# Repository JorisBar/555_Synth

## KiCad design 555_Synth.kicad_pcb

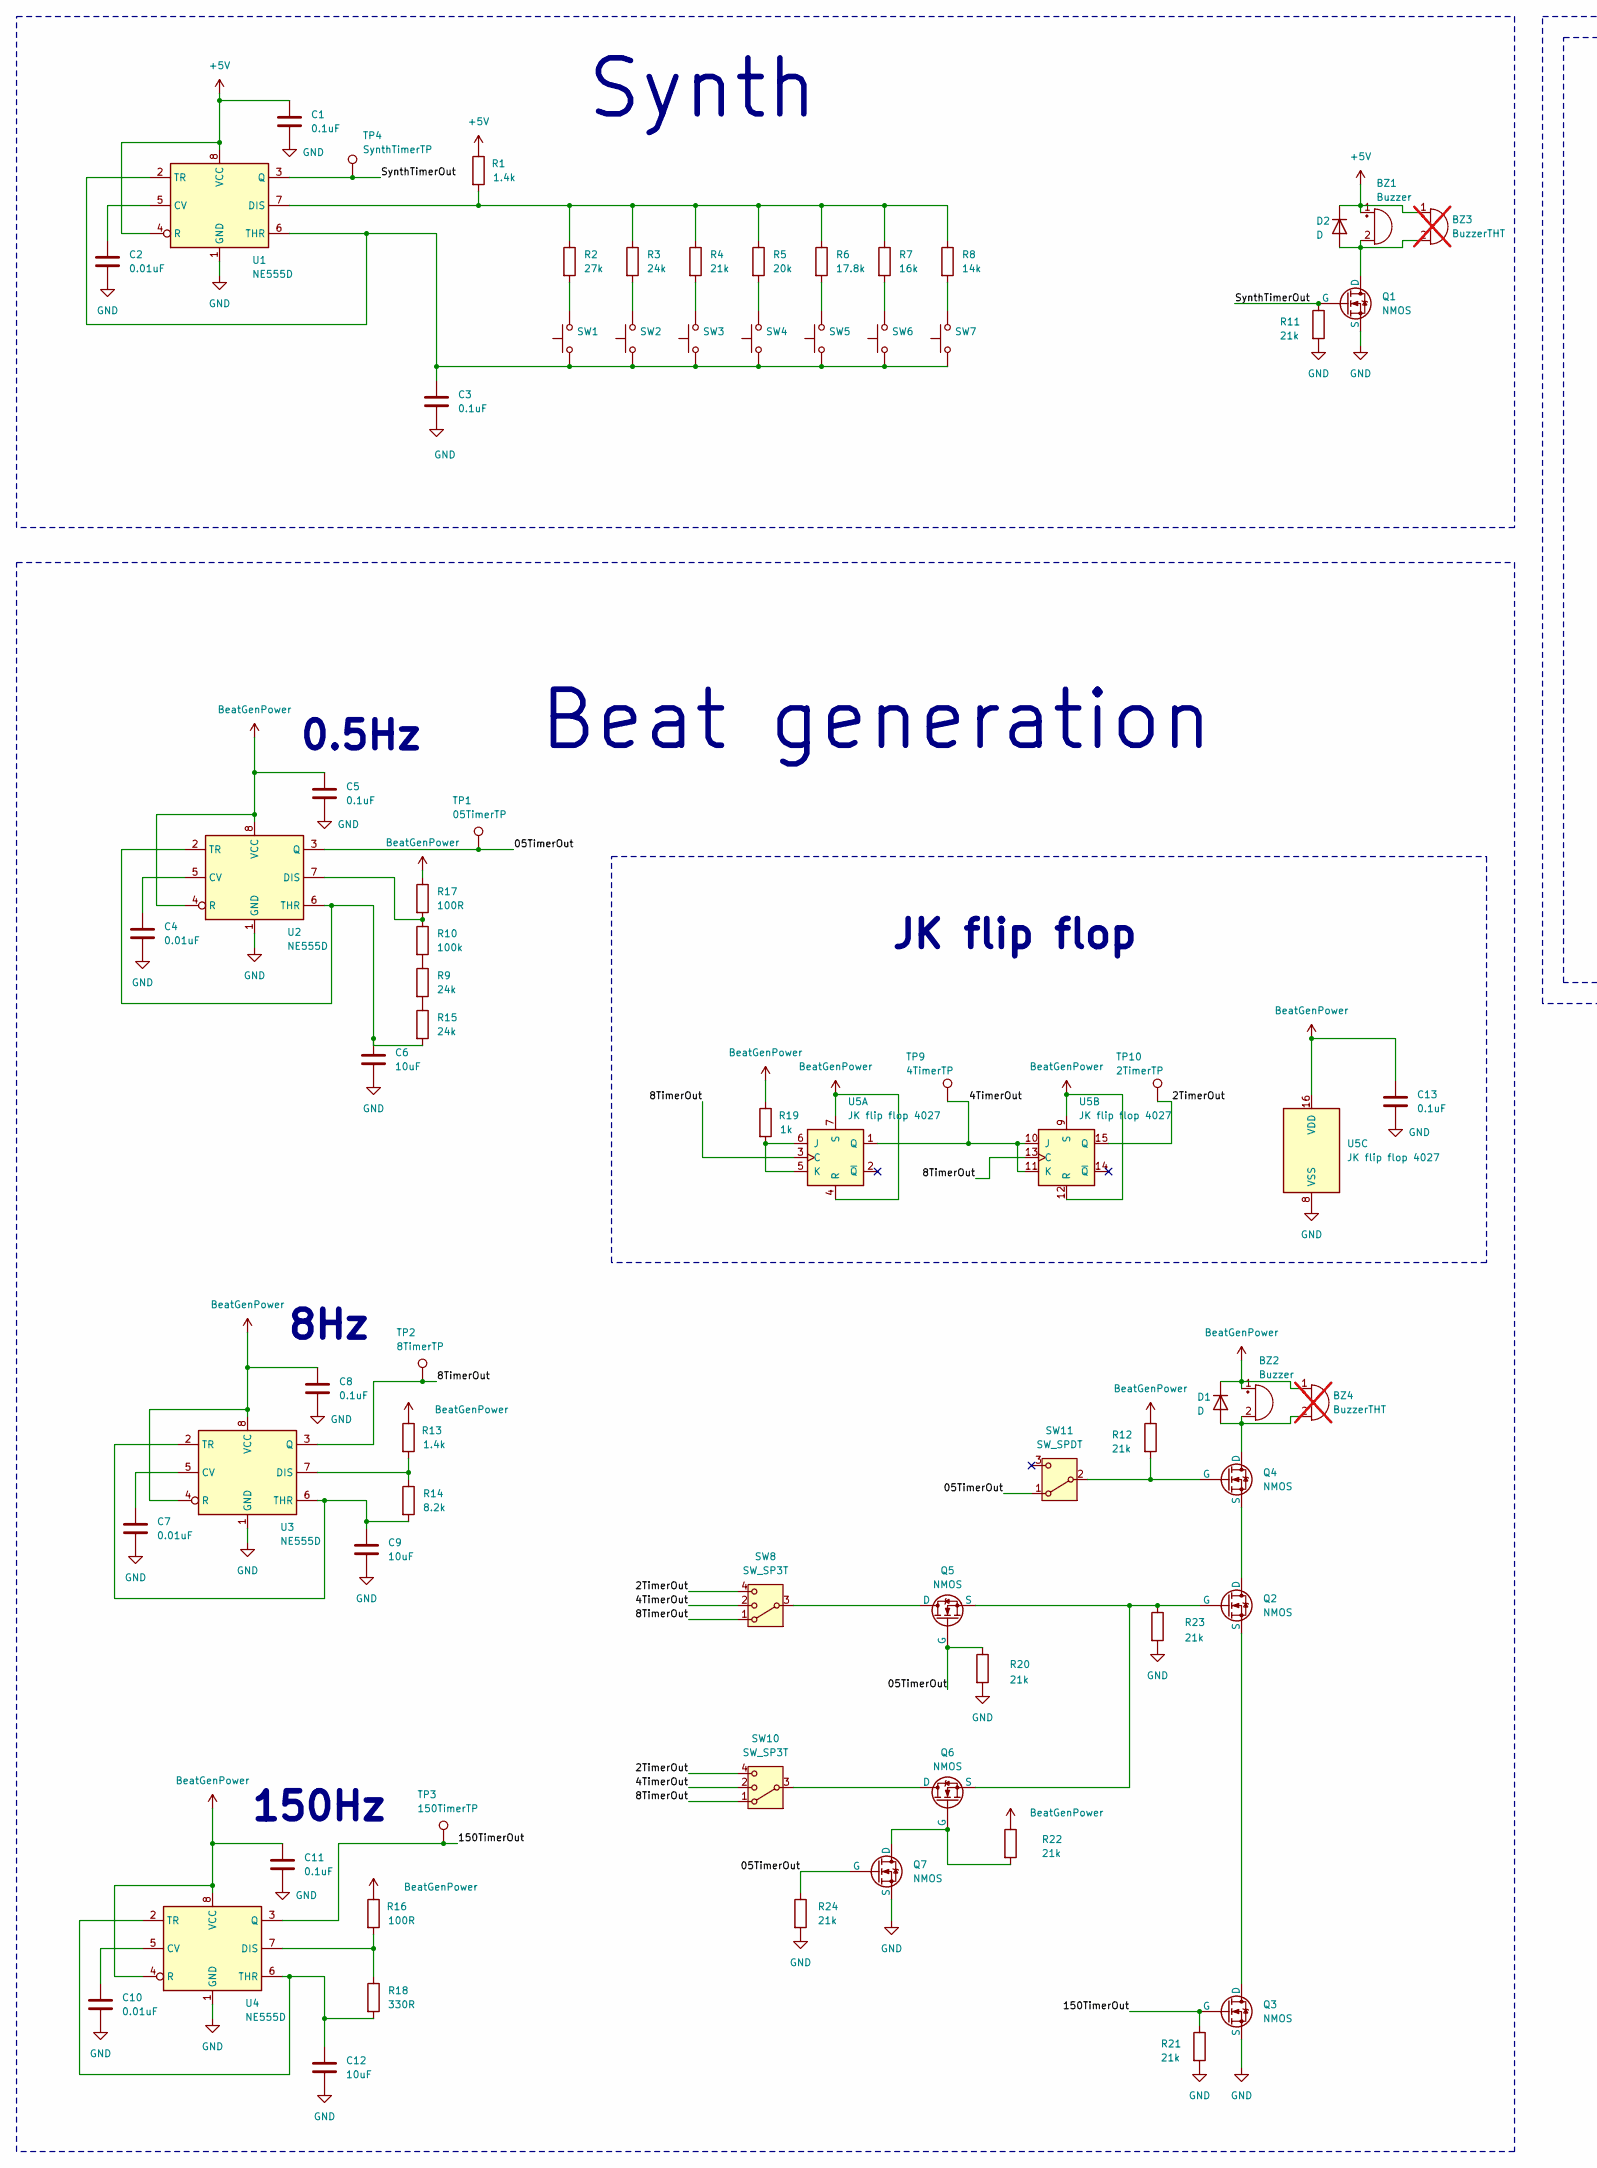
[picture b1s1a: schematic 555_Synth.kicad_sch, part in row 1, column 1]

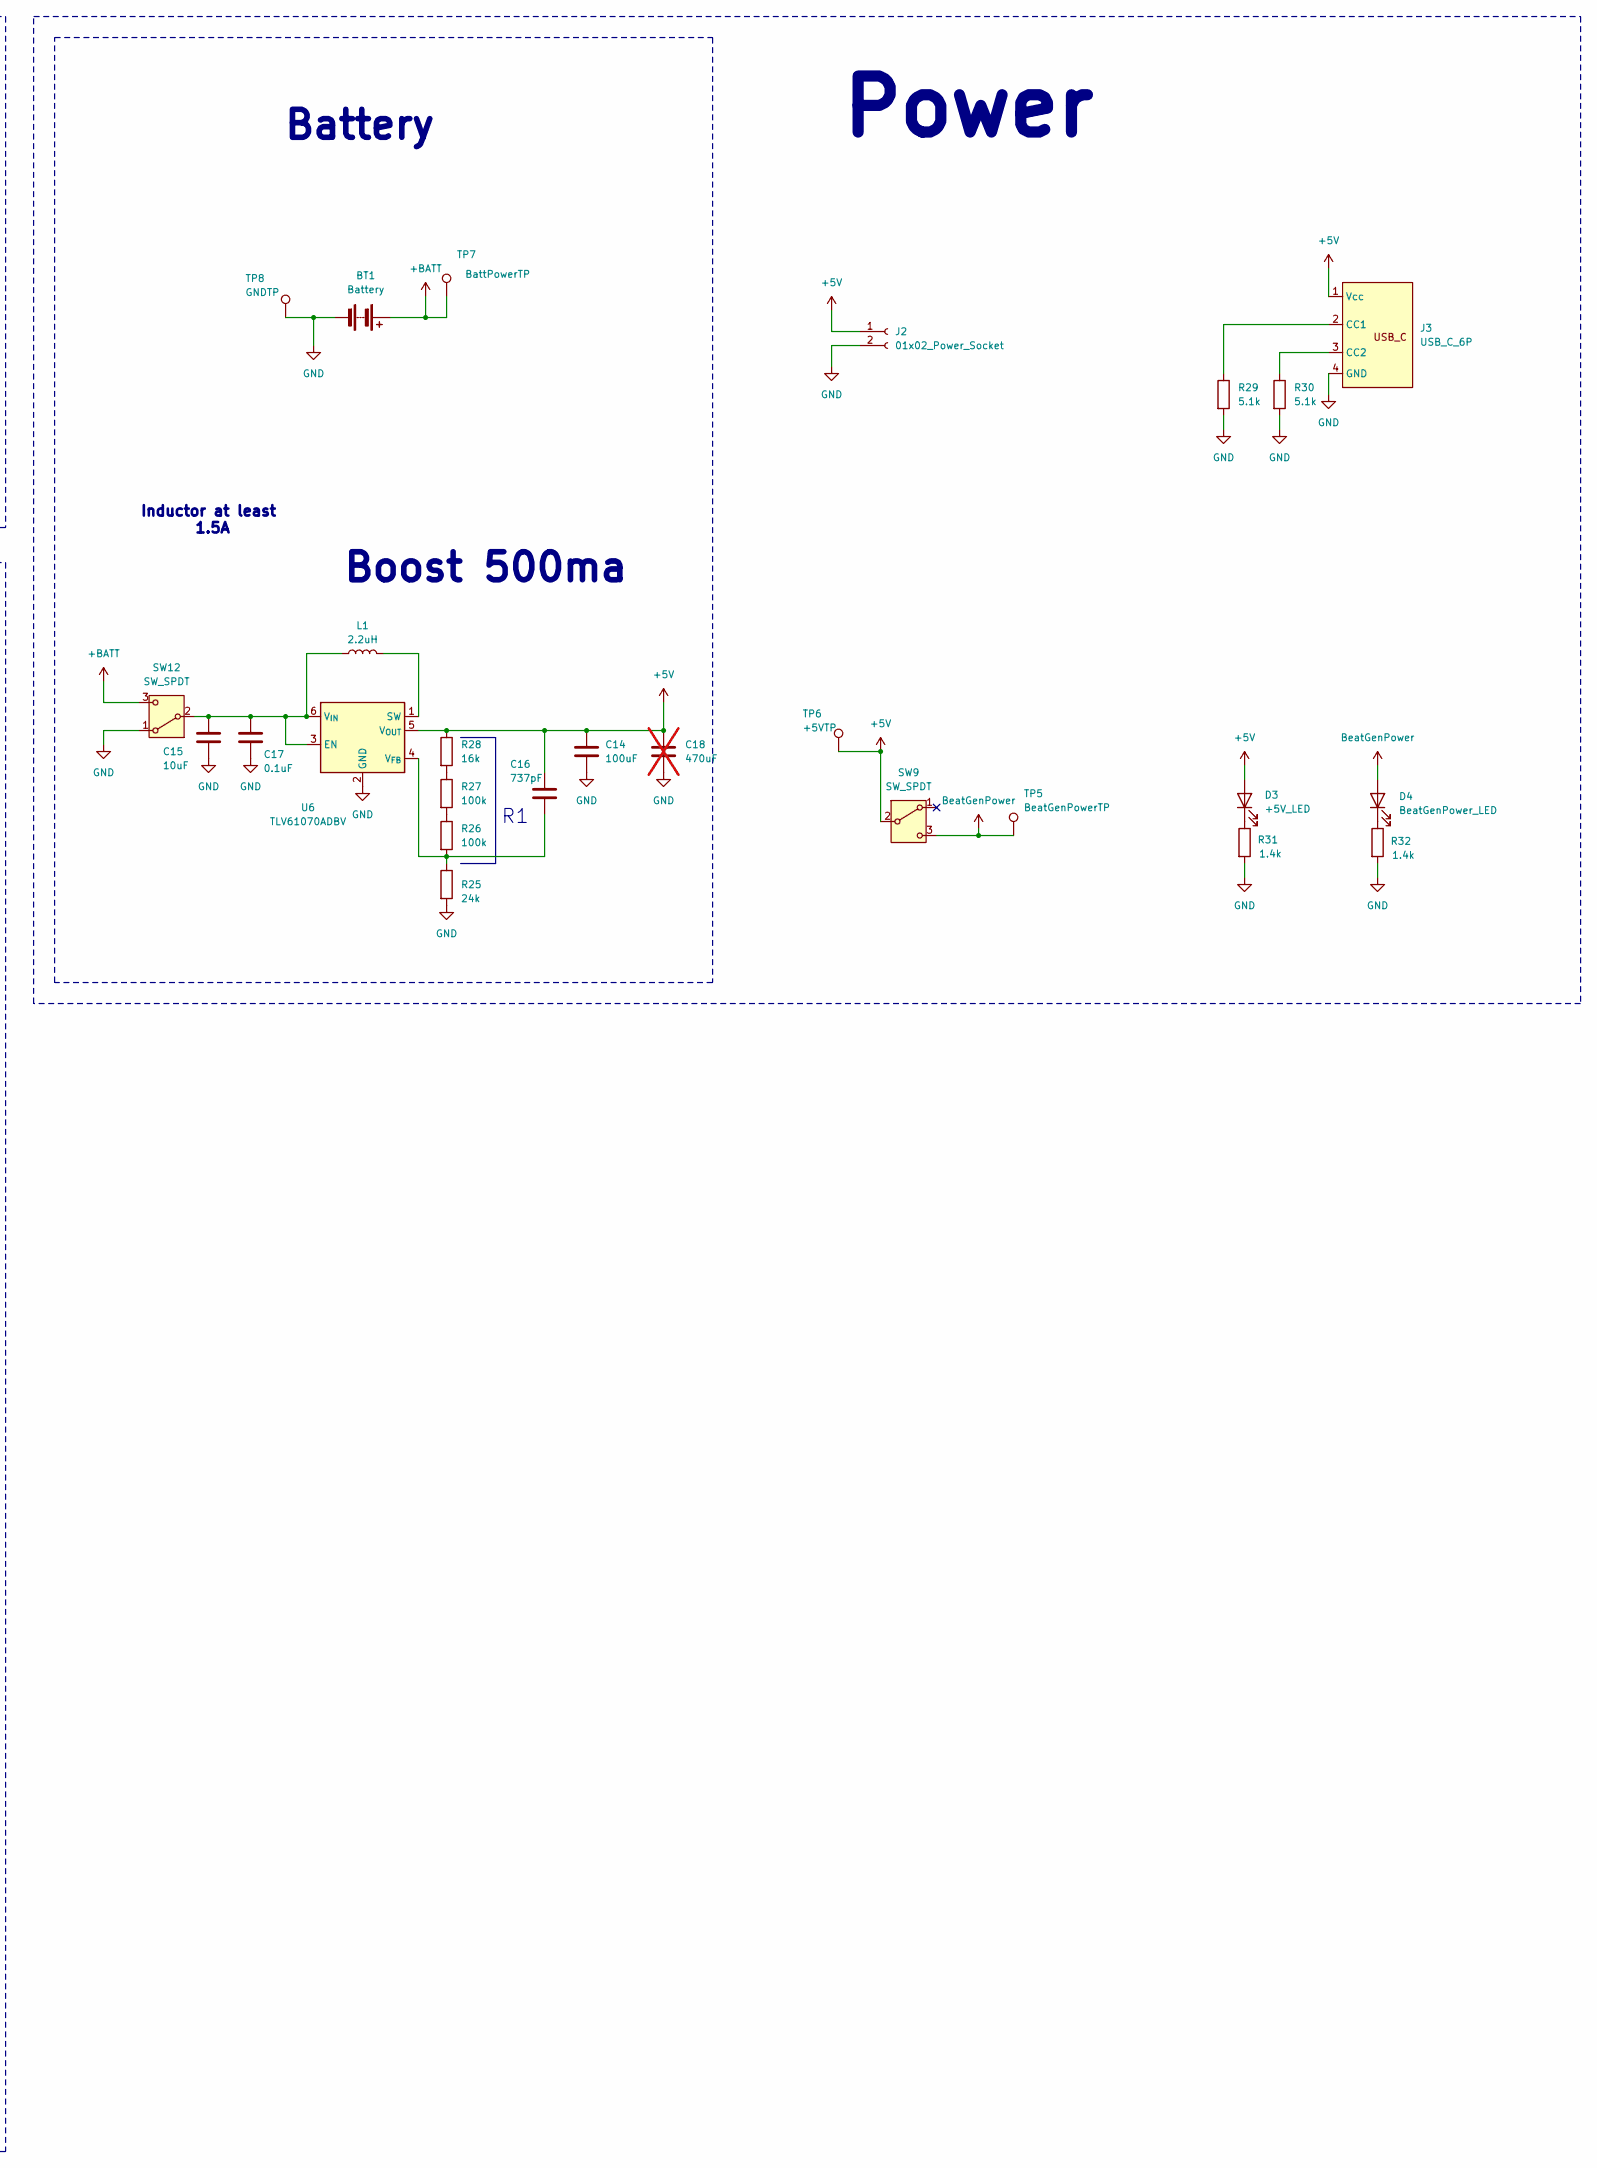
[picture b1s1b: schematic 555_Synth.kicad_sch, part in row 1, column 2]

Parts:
BT1: Battery; Battery holder pad and tension release
BZ1, BZ2: Buzzer; SMD buzzer passive square
BZ3, BZ4: BuzzerTHT; THT buzzer passive round; not fitted
C1, C3, C5, C8, C11, C13, C17: 0.1uF; C_0603_1608Metric_Pad1.08x0.95mm_HandSolder
C2, C4, C7, C10: 0.01uF; C_0603_1608Metric_Pad1.08x0.95mm_HandSolder
C6, C9, C12, C15: 10uF; C_0603_1608Metric_Pad1.08x0.95mm_HandSolder
C14: 100uF; CP_Elec_6.3x7.7
C16: 737pF; C_0603_1608Metric_Pad1.08x0.95mm_HandSolder
C18: 470uF; CP_Elec_8x10.5; not fitted
D1, D2: D; D_SOD-123F
D3: +5V_LED; LED_0603_1608Metric_Pad1.05x0.95mm_HandSolder
D4: BeatGenPower_LED; LED_0603_1608Metric_Pad1.05x0.95mm_HandSolder
J2: 01x02_Power_Socket; PinHeader_1x02_P2.54mm_Vertical
J3: USB_C_6P; USB_C_6P_Connetor
L1: 2.2uH; SMD 3x3.5mm inductor
Q1, Q2, Q3, Q4, Q5, Q6, Q7: NMOS; SOT-23_Handsoldering
R1, R13, R31, R32: 1.4k; R_0603_1608Metric_Pad0.98x0.95mm_HandSolder
R2: 27k; R_0603_1608Metric_Pad0.98x0.95mm_HandSolder
R3, R9, R15, R25: 24k; R_0603_1608Metric_Pad0.98x0.95mm_HandSolder
R4, R11, R12, R20, R21, R22, R23, R24: 21k; R_0603_1608Metric_Pad0.98x0.95mm_HandSolder
R5: 20k; R_0603_1608Metric_Pad0.98x0.95mm_HandSolder
R6: 17.8k; R_0603_1608Metric_Pad0.98x0.95mm_HandSolder
R7, R28: 16k; R_0603_1608Metric_Pad0.98x0.95mm_HandSolder
R8: 14k; R_0603_1608Metric_Pad0.98x0.95mm_HandSolder
R10, R26, R27: 100k; R_0603_1608Metric_Pad0.98x0.95mm_HandSolder
R14: 8.2k; R_0603_1608Metric_Pad0.98x0.95mm_HandSolder
R16, R17: 100R; R_0603_1608Metric_Pad0.98x0.95mm_HandSolder
R18: 330R; R_0603_1608Metric_Pad0.98x0.95mm_HandSolder
R19: 1k; R_0603_1608Metric_Pad0.98x0.95mm_HandSolder
R29, R30: 5.1k; R_0603_1608Metric_Pad0.98x0.95mm_HandSolder
SW1, SW2, SW3, SW4, SW5, SW6, SW7: SW_Push; SW_Push 6x6mm
SW8, SW10: SW_SP3T; SP3T slide switch THT
SW9, SW11, SW12: SW_SPDT; SPDT slide switch THT
TP1: 05TimerTP; TestPoint_Pad_D1.5mm
TP2: 8TimerTP; TestPoint_Pad_D1.5mm
TP3: 150TimerTP; TestPoint_Pad_D1.5mm
TP4: SynthTimerTP; TestPoint_Pad_D1.5mm
TP5: BeatGenPowerTP; TestPoint_Pad_1.5x1.5mm
TP6: +5VTP; TestPoint_Pad_1.5x1.5mm
TP7: BattPowerTP; TestPoint_Pad_1.5x1.5mm
TP8: GNDTP; TestPoint_Pad_1.5x1.5mm
TP9: 4TimerTP; TestPoint_Pad_D1.5mm
TP10: 2TimerTP; TestPoint_Pad_D1.5mm
U1, U2, U3, U4: NE555D; SOIC-8_3.9x4.9mm_P1.27mm
U5: JK flip flop 4027; SOP-16_4.4x10.4mm_P1.27mm
U6: TLV61070ADBV; SOT-23-6

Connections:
+5V: BZ1.1 (+), BZ3.1 (+), C1.1, C14.1, C16.1, C18.1, D2.1 (K), D3.2 (A), J2.1, J3.1 (Vcc), R1.1, R28.1, SW9.2 (B), TP6.1, U1.4 (R), U1.8 (VCC), U6.5 (V_{OUT})
+BATT: BT1.1 (+), SW12.3 (C), TP7.1
/2TimerOut: SW8.4, SW10.4, TP10.1, U5.15 (Q); also elsewhere on the board
/4TimerOut: SW8.2, SW10.2, TP9.1, U5.1 (Q), U5.10 (J), U5.11 (K); also elsewhere on the board
/05TimerOut: Q5.2 (G), Q7.2 (G), R20.1, R24.1, SW11.1 (A), TP1.1, U2.3 (Q); also elsewhere on the board
/8TimerOut: SW8.1, SW10.1, TP2.1, U3.3 (Q), U5.3 (C), U5.13 (C); also elsewhere on the board
/150TimerOut: Q3.2 (G), R21.1, TP3.1, U4.3 (Q); also elsewhere on the board
/SynthTimerOut: Q1.2 (G), R11.1, TP4.1, U1.3 (Q); also elsewhere on the board
BeatGenPower: BZ2.1 (+), BZ4.1 (+), C5.1, C8.1, C11.1, C13.1, D1.1 (K), D4.2 (A), R12.1, R13.1, R16.1, R17.1, R19.1, R22.1, SW9.3 (C), TP5.1, U2.4 (R), U2.8 (VCC), U3.4 (R), U3.8 (VCC), U4.4 (R), U4.8 (VCC), U5.4 (R), U5.7 (S), U5.9 (S), U5.12 (R), U5.16 (VDD)
GND: BT1.2 (-), C1.2, C2.2, C3.2, C4.2, C5.2, C6.2, C7.2, C8.2, C9.2, C10.2, C11.2, C12.2, C13.2, C14.2, C15.2, C17.2, C18.2, J2.2, J3.4 (GND), Q1.3 (S), Q3.3 (S), Q7.3 (S), R11.2, R20.2, R21.2, R23.2, R24.2, R25.2, R29.2, R30.2, R31.2, R32.2, SW12.1 (A), TP8.1, U1.1 (GND), U2.1 (GND), U3.1 (GND), U4.1 (GND), U5.8 (VSS), U6.2 (GND)
unnamed: BZ1.2 (-), BZ3.2 (-), D2.2 (A), Q1.1 (D)
unnamed: BZ2.2 (-), BZ4.2 (-), D1.2 (A), Q4.1 (D)
unnamed: D3.1 (K), R31.1
unnamed: D4.1 (K), R32.1
unnamed: J3.2 (CC1), R29.1
unnamed: J3.3 (CC2), R30.1
unnamed: Q2.1 (D), Q4.3 (S)
unnamed: Q2.2 (G), Q5.3 (S), Q6.3 (S), R23.1
unnamed: Q2.3 (S), Q3.1 (D)
unnamed: Q4.2 (G), R12.2, SW11.2 (B)
unnamed: Q5.1 (D), SW8.3
unnamed: Q6.1 (D), SW10.3
unnamed: Q6.2 (G), Q7.1 (D), R22.2
unnamed: R2.2, SW1.2
unnamed: R3.2, SW2.2
unnamed: R4.2, SW3.2
unnamed: R5.2, SW4.2
unnamed: R6.2, SW5.2
unnamed: R7.2, SW6.2
unnamed: R8.2, SW7.2
unnamed: R9.1, R10.2
unnamed: R9.2, R15.1
unnamed: R26.1, R27.2
unnamed: R27.1, R28.2
unnamed: C15.1, C17.1, L1.1, SW12.2 (B), U6.3 (EN), U6.6 (V_{IN})
unnamed: C2.1, U1.5 (CV)
unnamed: R1.2, R2.1, R3.1, R4.1, R5.1, R6.1, R7.1, R8.1, U1.7 (DIS)
unnamed: C3.1, SW1.1, SW2.1, SW3.1, SW4.1, SW5.1, SW6.1, SW7.1, U1.2 (TR), U1.6 (THR)
unnamed: C4.1, U2.5 (CV)
unnamed: R10.1, R17.2, U2.7 (DIS)
unnamed: C6.1, R15.2, U2.2 (TR), U2.6 (THR)
unnamed: C7.1, U3.5 (CV)
unnamed: R13.2, R14.1, U3.7 (DIS)
unnamed: C9.1, R14.2, U3.2 (TR), U3.6 (THR)
unnamed: C10.1, U4.5 (CV)
unnamed: R16.2, R18.1, U4.7 (DIS)
unnamed: C12.1, R18.2, U4.2 (TR), U4.6 (THR)
unnamed: R19.2, U5.5 (K), U5.6 (J)
unnamed: L1.2, U6.1 (SW)
unnamed: C16.2, R25.1, R26.2, U6.4 (V_{FB})

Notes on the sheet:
8Hz
0.5Hz
Beat generation
Synth
Boost 500ma
Battery
150Hz
Power
JK flip flop
Inductor at least 1.5A

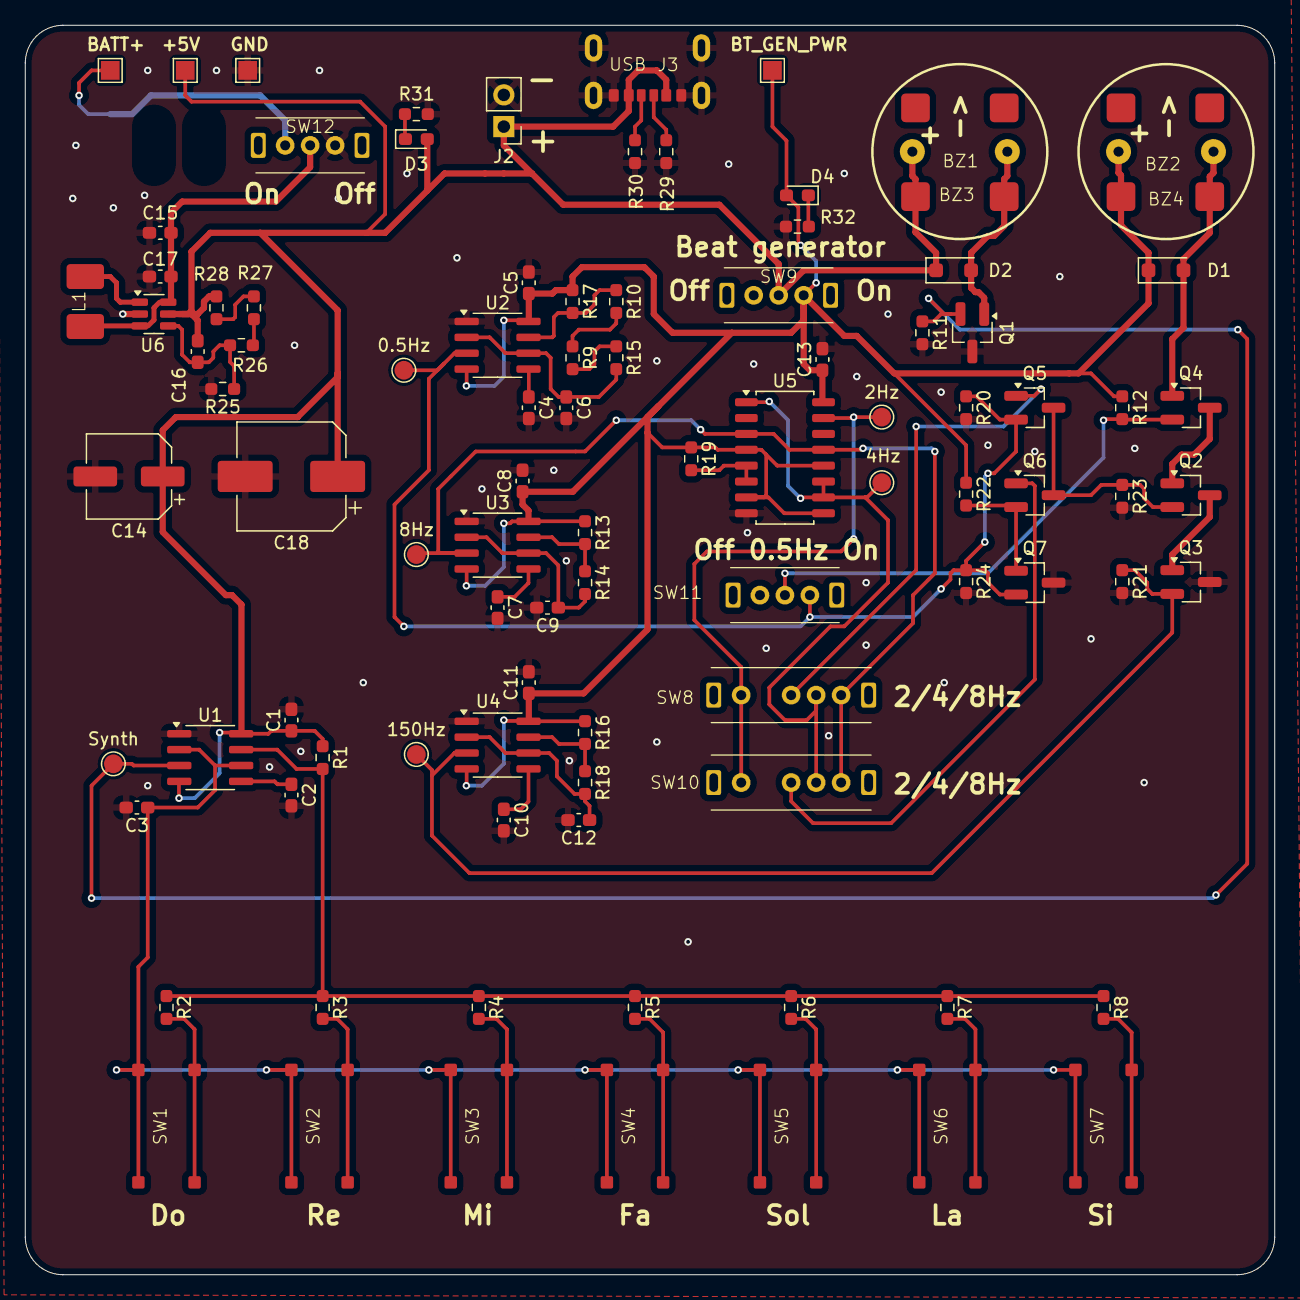
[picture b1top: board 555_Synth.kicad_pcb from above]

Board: 2 copper layers, 100.0 x 100.0 mm, 97 parts (1 on the bottom side), 50 nets.

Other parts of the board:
0.5Hz: 05TimerTP; TestPoint_Pad_D1.5mm
2Hz: 2TimerTP; TestPoint_Pad_D1.5mm
4Hz: 4TimerTP; TestPoint_Pad_D1.5mm
8Hz: 8TimerTP; TestPoint_Pad_D1.5mm
150Hz: 150TimerTP; TestPoint_Pad_D1.5mm
Synth: SynthTimerTP; TestPoint_Pad_D1.5mm

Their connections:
/2TimerOut: 2Hz.1; also elsewhere on the board
/4TimerOut: 4Hz.1; also elsewhere on the board
/05TimerOut: 0.5Hz.1; also elsewhere on the board
/8TimerOut: 8Hz.1; also elsewhere on the board
/150TimerOut: 150Hz.1; also elsewhere on the board
/SynthTimerOut: Synth.1; also elsewhere on the board

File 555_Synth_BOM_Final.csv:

Id;Designator;Footprint;Quantity;Designation;LCSC;Purchased quantity;Price;Cost/part;Cost/project
25;R19;R_0603_1608Metric_Pad0.98x0.95mm_HandSolder;1;1k;C2907002;100;0,07;0,0007;0,0007
16;R14;R_0603_1608Metric_Pad0.98x0.95mm_HandSolder;1;8.2k;C49653263;100;0,08;0,0008;0,0008
26;R2;R_0603_1608Metric_Pad0.98x0.95mm_HandSolder;1;27k;C3016359;100;0,08;0,0008;0,0008
28;R8;R_0603_1608Metric_Pad0.98x0.95mm_HandSolder;1;14k;C3016340;100;0,08;0,0008;0,0008
30;R18;R_0603_1608Metric_Pad0.98x0.95mm_HandSolder;1;330R;C49653542;100;0,08;0,0008;0,0008
32;R5;R_0603_1608Metric_Pad0.98x0.95mm_HandSolder;1;20k;C49653265;100;0,08;0,0008;0,0008
13;R6;R_0603_1608Metric_Pad0.98x0.95mm_HandSolder;1;17.8k;C2933161;100;0,09;0,0009;0,0009
6;R7,R28;R_0603_1608Metric_Pad0.98x0.95mm_HandSolder;2;16k;C3016344;100;0,08;0,0008;0,0016
9;R29,R30;R_0603_1608Metric_Pad0.98x0.95mm_HandSolder;2;5.1k;C49653001;100;0,08;0,0008;0,0016
34;R16,R17;R_0603_1608Metric_Pad0.98x0.95mm_HandSolder;2;100R;C3016239;100;0,08;0,0008;0,0016
4;R26,R10,R27;R_0603_1608Metric_Pad0.98x0.95mm_HandSolder;3;100k;C3016388;100;0,09;0,0009;0,0027
33;C16;C_0603_1608Metric_Pad1.08x0.95mm_HandSolder;1;737pF(680);C49326657;100;0,29;0,0029;0,0029
2;R9,R15,R25,R3;R_0603_1608Metric_Pad0.98x0.95mm_HandSolder;4;24k;C49653415;100;0,08;0,0008;0,0032
22;R13,R32,R1,R31;R_0603_1608Metric_Pad0.98x0.95mm_HandSolder;4;1.4k;C2930049;100;0,09;0,0009;0,0036
7;D3,D4;LED_0603_1608Metric_Pad1.05x0.95mm_HandSolder;2;LED;C965799;100;0,27;0,0027;0,0054
5;C2,C7,C4,C10;C_0603_1608Metric_Pad1.08x0.95mm_HandSolder;4;0.01uF;C7503504;100;0,17;0,0017;0,0068
1;R23,R4,R11,R12,R20,R21,R24,R22;R_0603_1608Metric_Pad0.98x0.95mm_HandSolder;8;21k;C2930076;100;0,09;0,0009;0,0072
8;D2,D1;D_SOD-123F;2;D;C2902912;100;0,37;0,0037;0,0074
3;C13,C8,C1,C3,C5,C17,C11;C_0603_1608Metric_Pad1.08x0.95mm_HandSolder;7;0.1uF;C6119867;100;0,16;0,0016;0,0112
11;C6,C9,C15,C12;C_0603_1608Metric_Pad1.08x0.95mm_HandSolder;4;10uF;C6119842;100;0,48;0,0048;0,0192
15;C14;CP_Elec_6.3x7.7;1;100uF;C22383804;20;0,45;0,0225;0,0225
14;J3;USB_C_6P_Connetor;1;USB_C_6P;C42400650;20;0,56;0,028;0,028
24;J2;PinHeader_1x02_P2.54mm_Vertical;1;01x02_Power_Socket;C49661;20;0,67;0,0335;0,0335
21;L1;SMD 3x3.5mm inductor;1;2.2uH;C41408464;10;0,43;0,043;0,043
29;C18;CP_Elec_8x10.5;1;470uF;C5162348;10;0,48;0,048;0,048
17;SW10,SW8;SP3T slide switch THT;2;SW_SP3T;C2681578;40;1,06;0,0265;0,053
23;SW9,SW11,SW12;SPDT slide switch THT;3;SW_SPDT;C22435632;40;0,77;0,01925;0,05775
27;BZ3,BZ4;THT buzzer passive round;2;BuzzerTHT;C49246967;10;0,36;0,036;0,072
19;SW7,SW1,SW2,SW6,SW4,SW3,SW5;SW_Push 6x6mm;7;SW_Push;C2837532;100;1,58;0,0158;0,1106
10;U4,U3,U1,U2;SOIC-8_3.9x4.9mm_P1.27mm;4;NE555D;C7529466;30;0,85;0,028333333;0,113333333
12;Q4,Q7,Q3,Q1,Q2,Q5,Q6;SOT-23_Handsoldering;7;NMOS;C49195711;20;0,37;0,0185;0,1295
18;U5;SOP-16_4.4x10.4mm_P1.27mm;1;JK flip flop 4027;C3007958;5;0,65;0,13;0,13
20;U6;SOT-23-6;1;TLV61070ADBV;C6881375;5;1,09;0,218;0,218
31;BZ2,BZ1;SMD buzzer passive square;2;Buzzer;C94599;10;1,67;0,167;0,334
35;BT1;Battery holder pad and tension release;1;Battery;;;;;
